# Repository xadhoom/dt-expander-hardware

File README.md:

## Eagle schematics and board files for Detectino hardware

These are design files for two piggy back boards used in the Detectino Alarm project.

### Detectino_nodcdc
This is an expansion board used to read analog and digital inputs from commercial
alarm sensors and provide readings over a shared CAN bus.

The core is an Arduino Nano. The board provides protection for analog
and digital signals, in order to harden Arduino inputs and a CAN bus
transceiver.

Each board can handle 8 analog sensors and 3 digital ones.

Multiple boards can be connected over a single CAN bus.

### dt-expander-v2
An updated board based on Detectino_nodcdc, where the 3 digital input have been removed,
analog inputs increased from 8 to 16, 2 relays outputs have been added, along with
6 Open Collector outputs.

To accomodate all needed I/O, the board is plugged with an Arduino Mega2650 Pro Mini:
http://wiki.epalsite.com/index.php?title=Mega2560_Pro_Mini

### Detectino_raspi
This is the "core" board, which is a piggy back for RaspberryPi B+,
which provides isolated CAN bus and isolated power supply using
a suitable DC-DC converter.

The board is completely isolated from the environment, in order
to protect the RaspberryPi where the core software runs and
avoid disruption of the service caused by external electrical factors.

This board is plugged in the same CAN bus and communicate with
the Detection expansion boards-

#### Warning!
I'm not an electronic expert at all, so I tried to understand
and do my best in designing these boards.
If someone finds any error or have suggestions, please tell!

##### Notes
The other folders are initial design of the Arduino piggy back board,
not realized in practice.

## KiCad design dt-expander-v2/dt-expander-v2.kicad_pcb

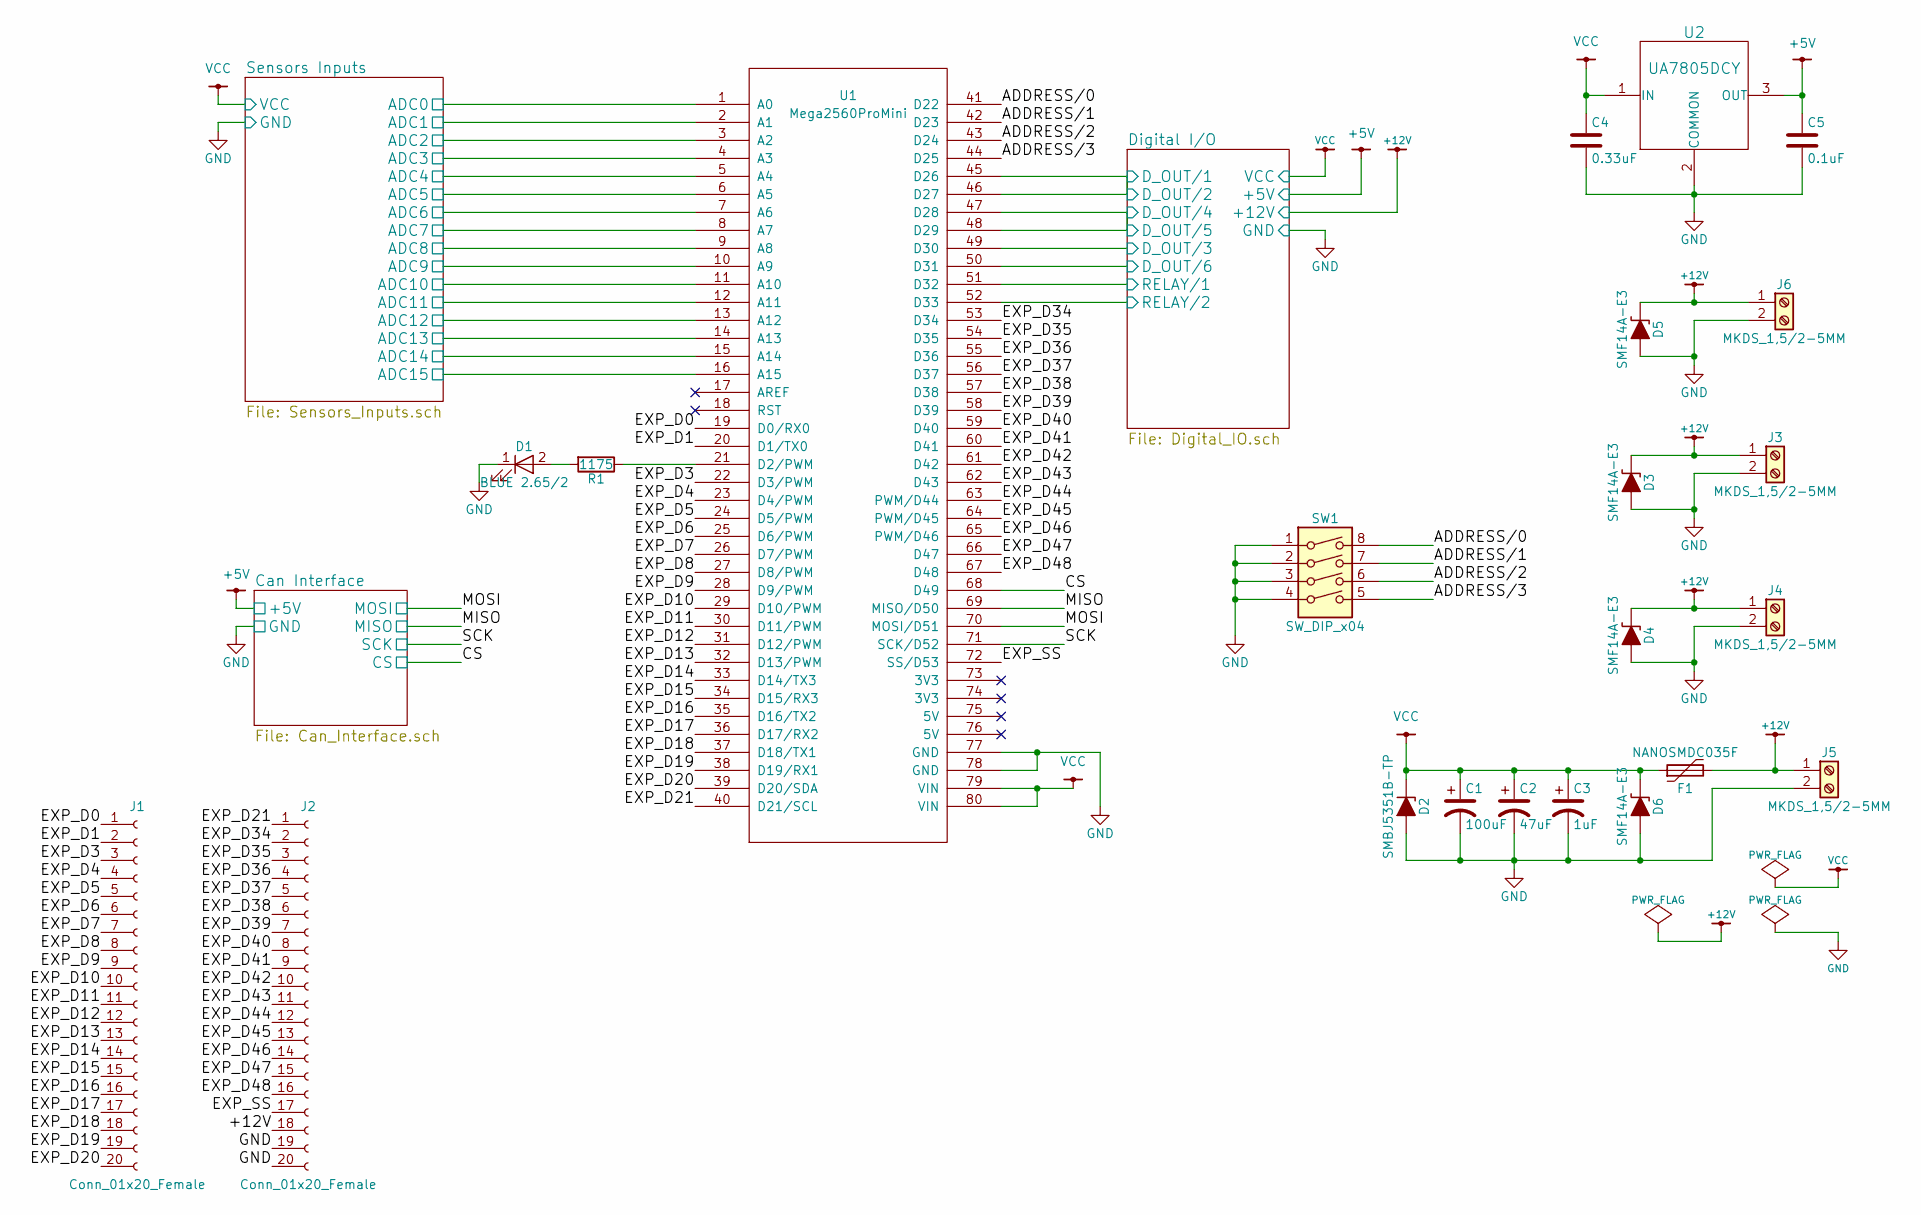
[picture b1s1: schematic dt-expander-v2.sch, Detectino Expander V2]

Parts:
C1: 100uF; CP_Radial_D6.3mm_P2.50mm
C2: 47uF; CP_Radial_D6.3mm_P2.50mm
C3: 1uF; CP_Radial_D4.0mm_P1.50mm
C4: 0.33uF; C_1206
C5: 0.1uF; C_1206
D1: BLUE 2.65/2; Led_1206
D2: SMBJ5351B-TP; do214aa
D3, D4, D5, D6: SMF14A-E3; do219ab
F1: NANOSMDC035F; Fuse_SMD1206_Wave
J1, J2: Conn_01x20_Female; Socket_Strip_Straight_1x20_Pitch2.54mm
J3, J4, J5, J6: MKDS_1,5/2-5MM; TerminalBlock_Pheonix_MKDS1.5-2pol
R1: 1175; R_0805
SW1: SW_DIP_x04; DIP-8_W7.62mm_LongPads
U1: Mega2560ProMini
U2: UA7805DCY; SOT-223-3Lead_TabPin2

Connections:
+5V: C5.1, U2.3 (OUT); also elsewhere on the board
+12V: D3.1 (A1), D4.1 (A1), D5.1 (A1), F1.2, J2.18, J3.1, J4.1, J5.1, J6.1; also elsewhere on the board
/ADDRESS/0: SW1.8, U1.41 (D22)
/ADDRESS/1: SW1.7, U1.42 (D23)
/ADDRESS/2: SW1.6, U1.43 (D24)
/ADDRESS/3: SW1.5, U1.44 (D25)
/CS: U1.68 (D49); also elsewhere on the board
/Digital I/O/D_OUT/1: U1.45 (D26), U1.46 (D27); also elsewhere on the board
/Digital I/O/D_OUT/3: U1.49 (D30); also elsewhere on the board
/Digital I/O/D_OUT/4: U1.47 (D28), U1.48 (D29); also elsewhere on the board
/Digital I/O/D_OUT/6: U1.50 (D31); also elsewhere on the board
/Digital I/O/RELAY/1: U1.51 (D32); also elsewhere on the board
/Digital I/O/RELAY/2: U1.52 (D33); also elsewhere on the board
/EXP_D0: J1.1, U1.19 (D0/RX0)
/EXP_D1: J1.2, U1.20 (D1/TX0)
/EXP_D3: J1.3, U1.22 (D3/PWM)
/EXP_D4: J1.4, U1.23 (D4/PWM)
/EXP_D5: J1.5, U1.24 (D5/PWM)
/EXP_D6: J1.6, U1.25 (D6/PWM)
/EXP_D7: J1.7, U1.26 (D7/PWM)
/EXP_D8: J1.8, U1.27 (D8/PWM)
/EXP_D9: J1.9, U1.28 (D9/PWM)
/EXP_D10: J1.10, U1.29 (D10/PWM)
/EXP_D11: J1.11, U1.30 (D11/PWM)
/EXP_D12: J1.12, U1.31 (D12/PWM)
/EXP_D13: J1.13, U1.32 (D13/PWM)
/EXP_D14: J1.14, U1.33 (D14/TX3)
/EXP_D15: J1.15, U1.34 (D15/RX3)
/EXP_D16: J1.16, U1.35 (D16/TX2)
/EXP_D17: J1.17, U1.36 (D17/RX2)
/EXP_D18: J1.18, U1.37 (D18/TX1)
/EXP_D19: J1.19, U1.38 (D19/RX1)
/EXP_D20: J1.20, U1.39 (D20/SDA)
/EXP_D21: J2.1, U1.40 (D21/SCL)
/EXP_D34: J2.2, U1.53 (D34)
/EXP_D35: J2.3, U1.54 (D35)
/EXP_D36: J2.4, U1.55 (D36)
/EXP_D37: J2.5, U1.56 (D37)
/EXP_D38: J2.6, U1.57 (D38)
/EXP_D39: J2.7, U1.58 (D39)
/EXP_D40: J2.8, U1.59 (D40)
/EXP_D41: J2.9, U1.60 (D41)
/EXP_D42: J2.10, U1.61 (D42)
/EXP_D43: J2.11, U1.62 (D43)
/EXP_D44: J2.12, U1.63 (PWM/D44)
/EXP_D45: J2.13, U1.64 (PWM/D45)
/EXP_D46: J2.14, U1.65 (PWM/D46)
/EXP_D47: J2.15, U1.66 (D47)
/EXP_D48: J2.16, U1.67 (D48)
/EXP_SS: J2.17, U1.72 (SS/D53)
/MISO: U1.69 (MISO/D50); also elsewhere on the board
/MOSI: U1.70 (MOSI/D51); also elsewhere on the board
/SCK: U1.71 (SCK/D52); also elsewhere on the board
/Sensors Inputs/ADC0: U1.1 (A0); also elsewhere on the board
/Sensors Inputs/ADC1: U1.2 (A1); also elsewhere on the board
/Sensors Inputs/ADC2: U1.3 (A2); also elsewhere on the board
/Sensors Inputs/ADC3: U1.4 (A3); also elsewhere on the board
/Sensors Inputs/ADC4: U1.5 (A4); also elsewhere on the board
/Sensors Inputs/ADC5: U1.6 (A5); also elsewhere on the board
/Sensors Inputs/ADC6: U1.7 (A6); also elsewhere on the board
/Sensors Inputs/ADC7: U1.8 (A7); also elsewhere on the board
/Sensors Inputs/ADC8: U1.9 (A8); also elsewhere on the board
/Sensors Inputs/ADC9: U1.10 (A9); also elsewhere on the board
/Sensors Inputs/ADC10: U1.11 (A10); also elsewhere on the board
/Sensors Inputs/ADC11: U1.12 (A11); also elsewhere on the board
/Sensors Inputs/ADC12: U1.13 (A12); also elsewhere on the board
/Sensors Inputs/ADC13: U1.14 (A13); also elsewhere on the board
/Sensors Inputs/ADC14: U1.15 (A14); also elsewhere on the board
/Sensors Inputs/ADC15: U1.16 (A15); also elsewhere on the board
GND: C1.2, C2.2, C3.2, C4.2, C5.2, D1.1 (K), D2.2 (A), D3.2 (A2), D4.2 (A2), D5.2 (A2), D6.2 (A2), J2.19, J2.20, J3.2, J4.2, J5.2, J6.2, SW1.1, SW1.2, SW1.3, SW1.4, U1.77 (GND), U1.78 (GND), U2.2 (COMMON); also elsewhere on the board
unnamed: D1.2 (A), R1.2
unnamed: R1.1, U1.21 (D2/PWM)
VCC: C1.1, C2.1, C3.1, C4.1, D2.1 (K), D6.1 (A1), F1.1, U1.79 (VIN), U1.80 (VIN), U2.1 (IN); also elsewhere on the board

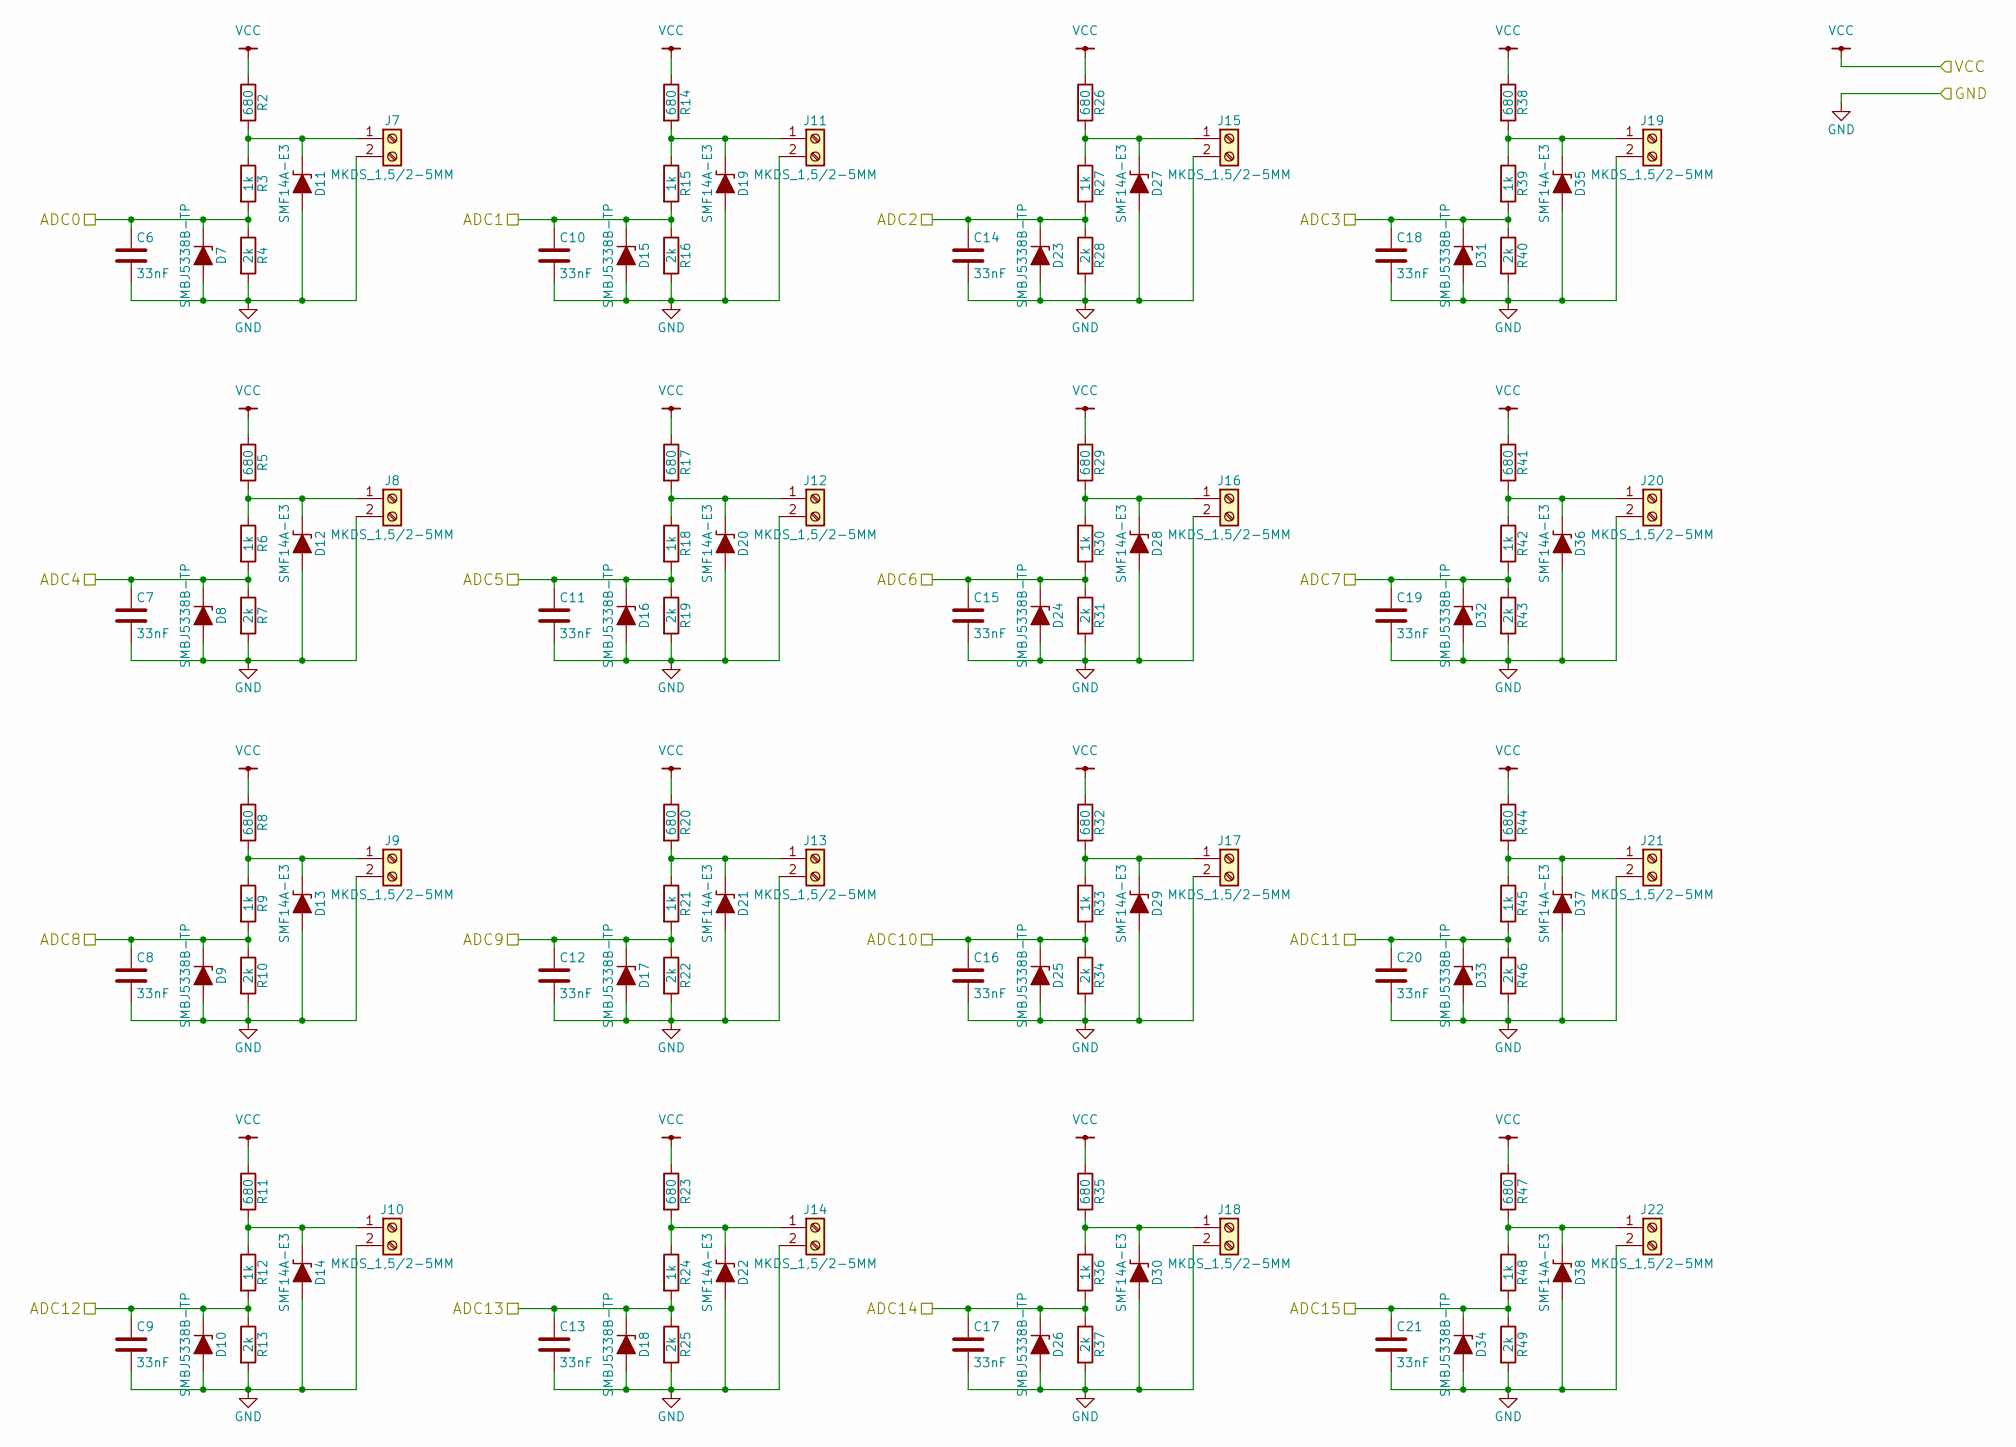
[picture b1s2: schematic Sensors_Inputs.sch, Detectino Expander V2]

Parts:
C6, C7, C8, C9, C10, C11, C12, C13, C14, C15, C16, C17, C18, C19, C20, C21: 33nF; C_1206
D7, D8, D9, D10, D15, D16, D17, D18, D23, D24, D25, D26, D31, D32, D33, D34: SMBJ5338B-TP; do214aa
D11, D12, D13, D14, D19, D20, D21, D22, D27, D28, D29, D30, D35, D36, D37, D38: SMF14A-E3; do219ab
J7, J8, J9, J10, J11, J12, J13, J14, J15, J16, J17, J18, J19, J20, J21, J22: MKDS_1,5/2-5MM; TerminalBlock_Pheonix_MKDS1.5-2pol
R2, R5, R8, R11, R14, R17, R20, R23, R26, R29, R32, R35, R38, R41, R44, R47: 680; R_0805
R3, R6, R9, R12, R15, R18, R21, R24, R27, R30, R33, R36, R39, R42, R45, R48: 1k; R_0805
R4, R7, R10, R13, R16, R19, R22, R25, R28, R31, R34, R37, R40, R43, R46, R49: 2k; R_0805

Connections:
/Sensors Inputs/ADC0: C6.1, D7.1 (K), R3.2, R4.1; also elsewhere on the board
/Sensors Inputs/ADC1: C10.1, D15.1 (K), R15.2, R16.1; also elsewhere on the board
/Sensors Inputs/ADC2: C14.1, D23.1 (K), R27.2, R28.1; also elsewhere on the board
/Sensors Inputs/ADC3: C18.1, D31.1 (K), R39.2, R40.1; also elsewhere on the board
/Sensors Inputs/ADC4: C7.1, D8.1 (K), R6.2, R7.1; also elsewhere on the board
/Sensors Inputs/ADC5: C11.1, D16.1 (K), R18.2, R19.1; also elsewhere on the board
/Sensors Inputs/ADC6: C15.1, D24.1 (K), R30.2, R31.1; also elsewhere on the board
/Sensors Inputs/ADC7: C19.1, D32.1 (K), R42.2, R43.1; also elsewhere on the board
/Sensors Inputs/ADC8: C8.1, D9.1 (K), R9.2, R10.1; also elsewhere on the board
/Sensors Inputs/ADC9: C12.1, D17.1 (K), R21.2, R22.1; also elsewhere on the board
/Sensors Inputs/ADC10: C16.1, D25.1 (K), R33.2, R34.1; also elsewhere on the board
/Sensors Inputs/ADC11: C20.1, D33.1 (K), R45.2, R46.1; also elsewhere on the board
/Sensors Inputs/ADC12: C9.1, D10.1 (K), R12.2, R13.1; also elsewhere on the board
/Sensors Inputs/ADC13: C13.1, D18.1 (K), R24.2, R25.1; also elsewhere on the board
/Sensors Inputs/ADC14: C17.1, D26.1 (K), R36.2, R37.1; also elsewhere on the board
/Sensors Inputs/ADC15: C21.1, D34.1 (K), R48.2, R49.1; also elsewhere on the board
GND: C6.2, C7.2, C8.2, C9.2, C10.2, C11.2, C12.2, C13.2, C14.2, C15.2, C16.2, C17.2, C18.2, C19.2, C20.2, C21.2, D7.2 (A), D8.2 (A), D9.2 (A), D10.2 (A), D11.2 (A2), D12.2 (A2), D13.2 (A2), D14.2 (A2), D15.2 (A), D16.2 (A), D17.2 (A), D18.2 (A), D19.2 (A2), D20.2 (A2), D21.2 (A2), D22.2 (A2), D23.2 (A), D24.2 (A), D25.2 (A), D26.2 (A), D27.2 (A2), D28.2 (A2), D29.2 (A2), D30.2 (A2), D31.2 (A), D32.2 (A), D33.2 (A), D34.2 (A), D35.2 (A2), D36.2 (A2), D37.2 (A2), D38.2 (A2), J7.2, J8.2, J9.2, J10.2, J11.2, J12.2, J13.2, J14.2, J15.2, J16.2, J17.2, J18.2, J19.2, J20.2, J21.2, J22.2, R4.2, R7.2, R10.2, R13.2, R16.2, R19.2, R22.2, R25.2, R28.2, R31.2, R34.2, R37.2, R40.2, R43.2, R46.2, R49.2; also elsewhere on the board
unnamed 82: D11.1 (A1), J7.1, R2.2, R3.1; also elsewhere on the board
unnamed 83: D12.1 (A1), J8.1, R5.2, R6.1; also elsewhere on the board
unnamed 84: D13.1 (A1), J9.1, R8.2, R9.1; also elsewhere on the board
unnamed 85: D14.1 (A1), J10.1, R11.2, R12.1; also elsewhere on the board
unnamed 86: D19.1 (A1), J11.1, R14.2, R15.1; also elsewhere on the board
unnamed 87: D20.1 (A1), J12.1, R17.2, R18.1; also elsewhere on the board
unnamed 88: D21.1 (A1), J13.1, R20.2, R21.1; also elsewhere on the board
unnamed 89: D22.1 (A1), J14.1, R23.2, R24.1; also elsewhere on the board
unnamed 90: D27.1 (A1), J15.1, R26.2, R27.1; also elsewhere on the board
unnamed 91: D28.1 (A1), J16.1, R29.2, R30.1; also elsewhere on the board
unnamed 92: D29.1 (A1), J17.1, R32.2, R33.1; also elsewhere on the board
unnamed 93: D30.1 (A1), J18.1, R35.2, R36.1; also elsewhere on the board
unnamed 94: D35.1 (A1), J19.1, R38.2, R39.1; also elsewhere on the board
unnamed 95: D36.1 (A1), J20.1, R41.2, R42.1; also elsewhere on the board
unnamed 96: D37.1 (A1), J21.1, R44.2, R45.1; also elsewhere on the board
unnamed 97: D38.1 (A1), J22.1, R47.2, R48.1; also elsewhere on the board
VCC: R2.1, R5.1, R8.1, R11.1, R14.1, R17.1, R20.1, R23.1, R26.1, R29.1, R32.1, R35.1, R38.1, R41.1, R44.1, R47.1; also elsewhere on the board

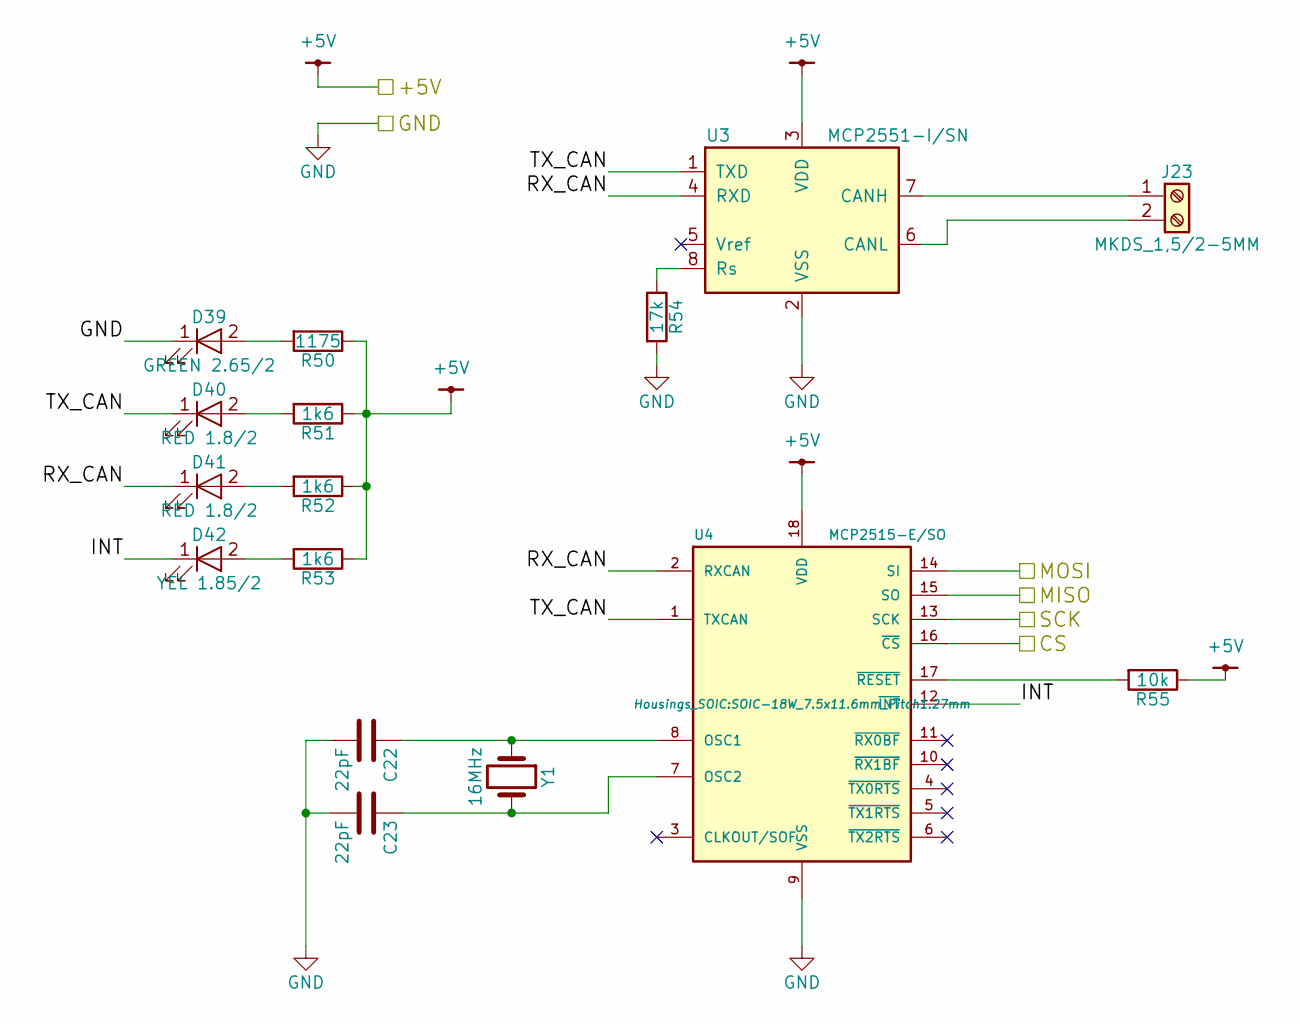
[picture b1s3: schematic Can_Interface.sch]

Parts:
C22, C23: 22pF; C_1206
D39: GREEN 2.65/2; Led_1206
D40, D41: RED 1.8/2; Led_1206
D42: YEL 1.85/2; Led_1206
J23: MKDS_1,5/2-5MM; TerminalBlock_Pheonix_MKDS1.5-2pol
R50: 1175; R_0805
R51, R52, R53: 1k6; R_0805
R54: 17k; R_0805
R55: 10k; R_0805
U3: MCP2551-I/SN; SOIC-8_3.9x4.9mm_Pitch1.27mm
U4: MCP2515-E/SO; SOIC-18W_7.5x11.6mm_Pitch1.27mm
Y1: 16MHz; Crystal_HC49-U_Vertical

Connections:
+5V: R50.1, R51.1, R52.1, R53.1, R55.1, U3.3 (VDD), U4.18 (VDD); also elsewhere on the board
/CS: U4.16 (~CS~); also elsewhere on the board
/Can Interface/INT: D42.1 (K), U4.12 (~INT~)
/Can Interface/RX_CAN: D41.1 (K), U3.4 (RXD), U4.2 (RXCAN)
/Can Interface/TX_CAN: D40.1 (K), U3.1 (TXD), U4.1 (TXCAN)
/MISO: U4.15 (SO); also elsewhere on the board
/MOSI: U4.14 (SI); also elsewhere on the board
/SCK: U4.13 (SCK); also elsewhere on the board
GND: C22.2, C23.2, D39.1 (K), R54.2, U3.2 (VSS), U4.9 (VSS); also elsewhere on the board
unnamed: C22.1, U4.8 (OSC1), Y1.1
unnamed: C23.1, U4.7 (OSC2), Y1.2
unnamed: D39.2 (A), R50.2
unnamed: D40.2 (A), R51.2
unnamed: D41.2 (A), R52.2
unnamed: D42.2 (A), R53.2
unnamed: J23.1, U3.7 (CANH)
unnamed: J23.2, U3.6 (CANL)
unnamed: R54.1, U3.8 (Rs)
unnamed: R55.2, U4.17 (~RESET~)

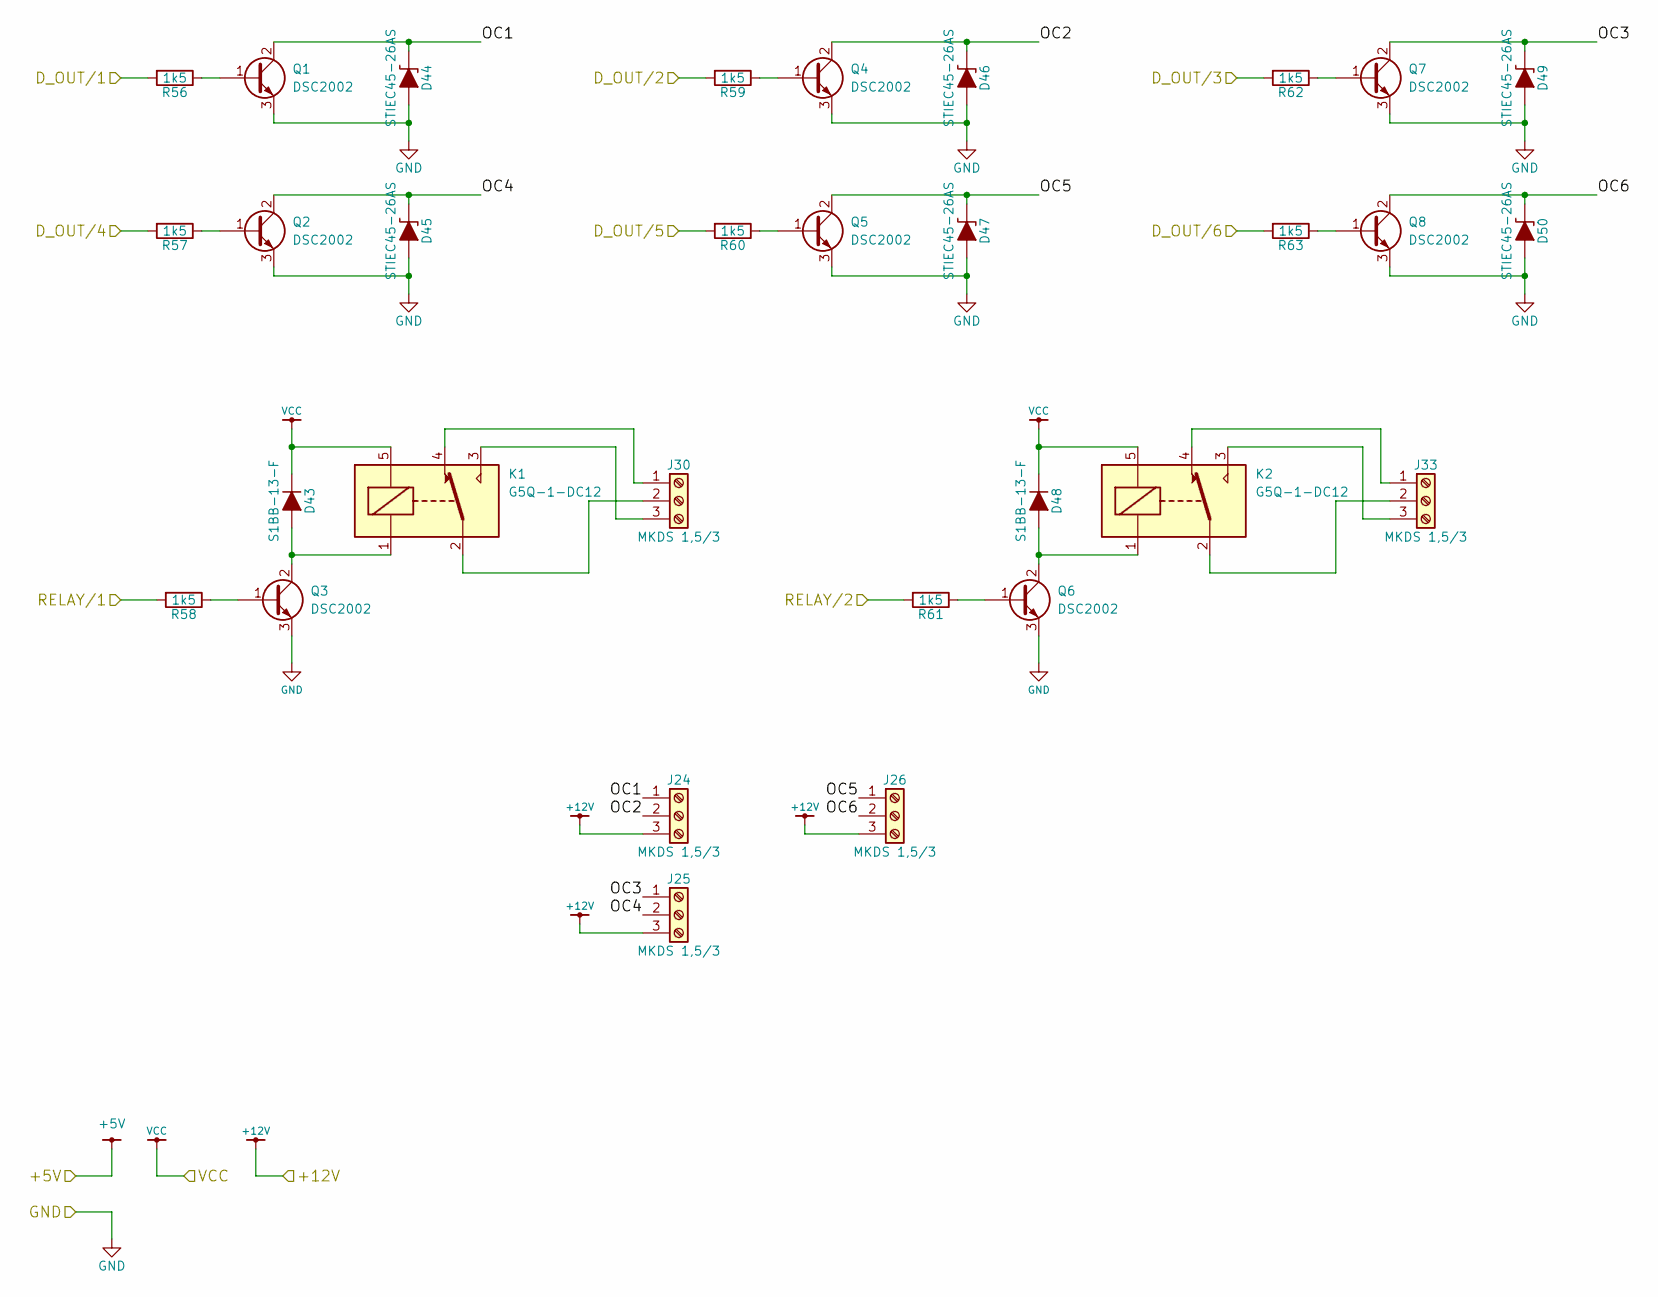
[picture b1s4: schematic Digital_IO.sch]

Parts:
D43, D48: S1BB-13-F; do214aa
D44, D45, D46, D47, D49, D50: STIEC45-26AS; do214ab
J24, J25, J26, J30, J33: MKDS 1,5/3; TerminalBlock_Pheonix_MKDS1.5-3pol
K1, K2: G5Q-1-DC12; Relay_SPDT_OMRON-G5Q
Q1, Q2, Q3, Q4, Q5, Q6, Q7, Q8: DSC2002; SOT-23
R56, R57, R58, R59, R60, R61, R62, R63: 1k5; R_0805

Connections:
+12V: J24.3, J25.3, J26.3; also elsewhere on the board
/Digital I/O/D_OUT/1: R56.2, R59.2; also elsewhere on the board
/Digital I/O/D_OUT/3: R62.2; also elsewhere on the board
/Digital I/O/D_OUT/4: R57.2, R60.2; also elsewhere on the board
/Digital I/O/D_OUT/6: R63.2; also elsewhere on the board
/Digital I/O/OC1: D44.1 (A1), J24.1, Q1.2 (C)
/Digital I/O/OC2: D46.1 (A1), J24.2, Q4.2 (C)
/Digital I/O/OC3: D49.1 (A1), J25.1, Q7.2 (C)
/Digital I/O/OC4: D45.1 (A1), J25.2, Q2.2 (C)
/Digital I/O/OC5: D47.1 (A1), J26.1, Q5.2 (C)
/Digital I/O/OC6: D50.1 (A1), J26.2, Q8.2 (C)
/Digital I/O/RELAY/1: R58.2; also elsewhere on the board
/Digital I/O/RELAY/2: R61.2; also elsewhere on the board
GND: D44.2 (A2), D45.2 (A2), D46.2 (A2), D47.2 (A2), D49.2 (A2), D50.2 (A2), Q1.3 (E), Q2.3 (E), Q3.3 (E), Q4.3 (E), Q5.3 (E), Q6.3 (E), Q7.3 (E), Q8.3 (E); also elsewhere on the board
unnamed: D43.2 (A), K1.1, Q3.2 (C)
unnamed: D48.2 (A), K2.1, Q6.2 (C)
unnamed: J30.1, K1.4
unnamed: J30.2, K1.2
unnamed: J30.3, K1.3
unnamed: J33.1, K2.4
unnamed: J33.2, K2.2
unnamed: J33.3, K2.3
unnamed: Q1.1 (B), R56.1
unnamed: Q2.1 (B), R57.1
unnamed: Q3.1 (B), R58.1
unnamed: Q4.1 (B), R59.1
unnamed: Q5.1 (B), R60.1
unnamed: Q6.1 (B), R61.1
unnamed: Q7.1 (B), R62.1
unnamed: Q8.1 (B), R63.1
VCC: D43.1 (K), D48.1 (K), K1.5, K2.5; also elsewhere on the board

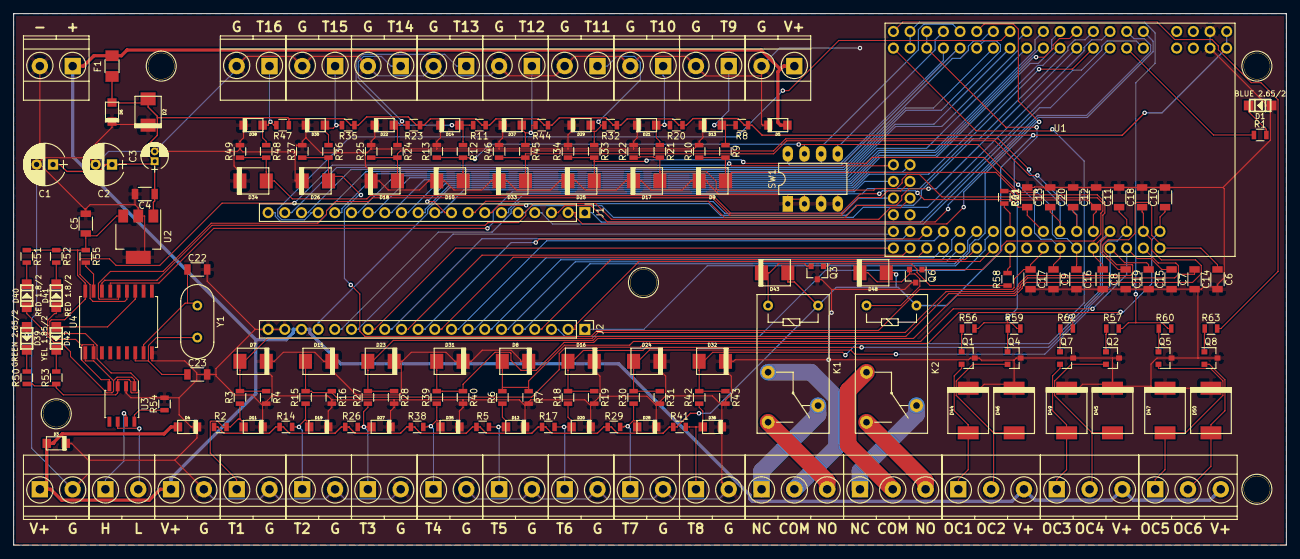
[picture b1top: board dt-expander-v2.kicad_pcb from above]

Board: 2 copper layers, 194.0 x 81.0 mm, 185 parts (0 on the bottom side), 124 nets.

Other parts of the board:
HOLE1, HOLE2, HOLE3, HOLE4: 1pin
T1, T2, T3, T4, T5, T6, T7, T8, T9, T10, T11, T12, T13, T14, T15, T16: MKDS_1,5/2-5MM; TerminalBlock_Pheonix_MKDS1.5-2pol

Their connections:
GND: T1.2, T2.2, T3.2, T4.2, T5.2, T6.2, T7.2, T8.2, T9.2, T10.2, T11.2, T12.2, T13.2, T14.2, T15.2, T16.2; also elsewhere on the board
unnamed 82: T1.1; also elsewhere on the board
unnamed 83: T5.1; also elsewhere on the board
unnamed 84: T9.1; also elsewhere on the board
unnamed 85: T13.1; also elsewhere on the board
unnamed 86: T2.1; also elsewhere on the board
unnamed 87: T6.1; also elsewhere on the board
unnamed 88: T10.1; also elsewhere on the board
unnamed 89: T14.1; also elsewhere on the board
unnamed 90: T3.1; also elsewhere on the board
unnamed 91: T7.1; also elsewhere on the board
unnamed 92: T11.1; also elsewhere on the board
unnamed 93: T15.1; also elsewhere on the board
unnamed 94: T4.1; also elsewhere on the board
unnamed 95: T8.1; also elsewhere on the board
unnamed 96: T12.1; also elsewhere on the board
unnamed 97: T16.1; also elsewhere on the board

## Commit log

2015-10-18 initial import
2015-10-18 more updates to readme
2017-10-15 kicad files for new board with 16 inputs, 2 relays and 6 open collectors outputs
